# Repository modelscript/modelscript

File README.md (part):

<div align="center"><b>بِسْمِ اللَّهِ الرَّحْمَٰنِ الرَّحِيمِ</b></div>
<div align="center">In the name of Allah, the Compassionate, the Merciful</div>

# ModelScript

ModelScript is a Web-native, polyglot compiler & engineering intelligence platform that unifies **106 open standards and industrial simulation formats** — spanning systems engineering & optimization (ModelScript, Modelica, AMPL, SysML v2, SSP, ReqIF, NIST OSCAL, OWL 2, CSV), power, RF, telecommunications & electronics (PSCAD, PSS/E, CIM / CGMES, OpenDSS, DIgSILENT PowerFactory, GE PSLF, OCPP, OpenADR, SPICE, Verilog-A, IBIS, Touchstone, Optical Transport, RAN & Microwave, Fiber Outside Plant), fluid/process, subsurface, civil water & nuclear (OLGA, PipelineStudio, Aspen Plus, gPROMS, ECLIPSE, EPANET, SWMM, RELAP5, EnergyPlus, HEC-RAS, TOUGH, MODFLOW, LandGEM), multibody/automotive/robotics/rail & transit (ADAMS, SIMPACK, GENSYS, GT-SUITE, SIMA, URDF, OpenDRIVE, OpenSCENARIO, AUTOSAR, GTFS, PLCopen, AutomationML), aerospace & controls (Simulink, EASY5, JSBSim, ROCETS, CCSDS), 3D CAD/CAE & metrology (STEP, ISO 23952 QIF, OpenSCAD, OpenUSD, CalculiX FEA, SU2 CFD), chemistry & systems/synthetic biology (SBML, Antimony, Cantera, SMILES/SDF, NMTRAN, SBOL3, BioNetGen, SED-ML, PDB/mmCIF, GenBank/FASTA, PHREEQC, Fortran, C99), and radiology, radiation oncology & computer-assisted surgery (OpenSim, DICOM-RT, CellML, FEBio/SOFA, NIfTI/NRRD, TOPAS/GATE, 3MF Medical, OpenIGTLink/PLUS) — into a continuous digital thread for end-to-end design, simulation, formal verification, and compliance auditing.

---

## Architecture Highlights

```
┌──────────────────────────────────────────────────────────────────────────────────────────┐
│                                 ModelScript Digital Thread                               │
├──────────────────┬─────────────────┬─────────────────┬─────────────────┬─────────────────┤
│ SysML v2 / ReqIF │ Modelica / SSP  │ STEP / QIF / CAD│ Power / Fluids  │ Bio / Medical / │
│  OSCAL / OWL 2   │ Simulink / EASY5│  (OpenSCAD/FEA) │ (PSCAD/OLGA/+)  │ Aero / Robotics │
└────────┬─────────┴────────┬────────┴────────┬────────┴────────┬────────┴────────┬────────┘
         │                  │                 │                 │                 │
         ▼                  ▼                 ▼                 ▼                 ▼
┌──────────────────────────────────────────────────────────────────────────────────────────┐
│                 Native WebAssembly GLR Incremental Parsers & CST Arenas                  │
├──────────────────────────────────────────────────────────────────────────────────────────┤
│                  Polyglot Triple Graph Grammars (TGG) & AOT Rewriting                    │
│           (Bidirectional forward/backward propagation & Critical Pair Analysis)          │
├──────────────────────────────────────────────────────────────────────────────────────────┤
│                      Salsa Query Engine & Workspace Symbol Index                         │
│                    (Incremental memoization, dependency invalidation)                    │
├──────────────────────────────────────────────────────────────────────────────────────────┤
│                       Semantic Theory Coordinator (Nelson-Oppen)                         │
│   Ontology ─── Constraint/Arithmetic ─── Abstract Domains ─── Continuous Safety ─── CAD  │
├──────────────────────────────────────────────────────────────────────────────────────────┤
│                        Data-Oriented DAE Arena & Solvers                                 │
│   DAEBuilder ── BLT ── SUNDIALS CVODE/IDA ── WebGPU Batched ── Direct Collocation Opt    │
└──────────────────────────────────────────────────────────────────────────────────────────┘
```

### 1. Polyglot Triple Graph Grammars (TGG)

ModelScript features a declarative, AOT-compiled **Triple Graph Grammar (TGG)** and Double-Pushout (DPO) graph rewriting engine (`@modelscript/dsl/tgg`). Rather than relying on fragile manual point-to-point synchronizers, TGG rules declaratively define correspondences between source, target, and correspondence graphs. The engine compiles these rules into high-performance AssemblyScript dispatch tables in WebAssembly (`tgg_forward_dispatch`, `tgg_backward_dispatch`, `tgg_propagate_all_stale`), verified for confluence and termination via integrated **Critical Pair Analysis (CPA)**.

### 2. Semantic Theory Coordinator (Nelson-Oppen Multi-Solver)

Cross-domain verification is orchestrated by a generalized **Nelson-Oppen Semantic Theory Coordinator** (`@modelscript/runtime/formal/theory_coordinator`), exchanging equality facts, tight numeric intervals, and conflict clauses across **19 domain theory oracles** with CDCL(T) case splitting:

- **Ontology Domain (`OntologyTheoryOracle`)**: Tableau Description Logic (DL) reasoner, OWL2 bundle closure, BFO ISO/IEC 21838-2 upper-level semantic alignment (`SemanticProjector`), concept subsumption, and scoped disjointness.
- **Constraint Domain (`ConstraintTheoryOracle`)**: Non-linear interval contraction via HC4 contractor, DPLL(T) arithmetic solver, and variable domain bounding.
- **Abstract Domain (`AbstractDomainOracle`)**: Octagon Difference Bound Matrices (DBM), 4D spatio-temporal intervals, and relational numerical bounds.
- **Continuous Safety & Reliability Domain (`ContinuousSafetyOracle` / `SafetyTheoryOracle`)**: Reachability analysis via zonotopes, constrained zonotopes, star sets, Sum-of-Squares (SOS) barrier certificates, Fault Tree Analysis (FTA), Minimal Cut Sets (MCS), and ISO 26262 / DO-178C safety metrics.
- **Dynamic Simulation Domain (`DynamicSimulationOracle`)**: DAE numerical trajectory integration, Signal Temporal Logic (STL) quantitative robustness monitoring, and tolerance propagation.
- **Spatial Physics Domain (`SpatialPhysicsOracle`)**: Watertight B-Rep CAD solid query, collision/clearance checks, geometric mass properties, 3D verification overlays (reachability tubes, SOS barrier shells, clearance vectors), and 3D FEA/CFD field coupling.
- **CAE Contract Domain (`CaeContractOracle`)**: FEA structural stress/deflection and CFD aerodynamic performance contract verification synchronized with the Digital Thread hypergraph.
- **Causalization Domain (`CausalizationOracle`)**: Pantelides Index-1 structural non-singularity, algebraic loop solvability, and Nyquist-Shannon sampling stability verification.
- **Dimensional Domain (`DimensionalOracle`)**: ISO 80000 7-element rational exponent vector (`[L, M, T, I, Θ, N, J]`) dimensional homogeneity, unit consistency, and cross-domain polyglot drift checking (`checkPolyglotPhysicalDrift`).
- **Entailment Domain (`EntailmentOracle`)**: V-Model requirements decomposition completeness proving ($\bigwedge R_{\text{child},i} \models R_{\text{parent}}$) with signed proof manifest generation.
- **Flow Algebra Domain (`FlowAlgebraOracle`)**: SysML v2 / KerML conjugated port involution (`~Port`), Kirchhoff conservative flow balancing, and 1D–3D CFD boundary flux coupling.
- **Tolerance Stack & UQ Domains (`ToleranceStackOracle`, `UqOracle`)**: STEP AP242 GD&T 1D/3D tolerance chain evaluation (Worst-Case, RSS, Six-Sigma $C_{pk}$) and stochastic Uncertainty Quantification via analytical CDFs and Monte Carlo sampling.
- **Radiology & Surgical CAS Domain (`RadiologyCasTheoryOracle`)**: QUANTEC organ-at-risk (OAR) radiotherapy DVH/BED/EQD2 dose constraints, Hadrontherapy Bragg peak range verification, $SE(3)$ surgical navigation transform orthogonality, Fitzpatrick Target Registration Error ($\text{TRE}$), and 2-manifold patient-specific cutting guide safety checks.
- **Additional Domain Oracles**: `ArrayTheoryOracle` (array read-over-write axioms), `BitVectorTheoryOracle` (fixed-width bit-vector arithmetic), `StringTheoryOracle` (string & regex constraints), `PowerGridTheoryOracle` (AC power flow & grid stability), `TelecomTheoryOracle` (RF MPE, DWDM GSNR & siting), `MarineMooringTheoryOracle` (catenary mooring & DNV-OS-E301), and `PressureVesselOracle` (ASME BPVC Sec. VIII Div. 1 pressure vessel rules) — see [`packages/runtime/README.md`](./packages/runtime/README.md).

### 3. Data-Oriented Linear Memory Simulation (DAE Arena)

The simulation runtime employs a zero-allocation Struct-of-Arrays (SoA) layout (`DAEBuilder`) in linear WebAssembly memory. Equations, variables, and expressions are lowered directly from linear parser CST nodes into integer arena handles, enabling microsecond Pantelides index reduction, Tarjan BLT partition sorting, alias elimination, Implicitly Restarted Arnoldi sparse eigenvalue extraction, and SIMD/WebGPU batched numerical solving without garbage collection overhead.

### 4. Salsa-Based Incremental Computation

Inspired by Rust's Salsa, compilation, name resolution, and specialized class instances are fully memoized on a demand-driven dependency graph. When an engineer modifies a single equation or parameter, only transitively affected queries and DAE blocks are re-flattened.

---

## Supported Languages & Domain Capabilities (106 Languages)

ModelScript provides first-class support for **106 engineering languages and simulation formats** under `languages/`, organized across 8 domain clusters and powered by native WebAssembly parsers, linear-memory CST arenas, static pre-flight linters, and direct `DAEBuilder` lowering.

> **Maturity Tiers** (enforced in `package.json#modelscript.tier` via `pnpm run lint:manifests` and audited via `pnpm run audit:languages`):
>
> - **`Beta` (33 languages)** — Production-ready with complete WASM GLR parser, static linter, DAE/solver lowering, and $\ge 8$ test suites verified against standard industry benchmarks or standard library snapshots (e.g., OpenModelica & MSL 4.1.0, OMG KerML standard library, IEEE/WECC power grids, US EPA EPANET/SWMM, Manchester Benchmark / EN 14363, NASA ROCETS / CCSDS).
> - **`Alpha` (72 languages)** — Domain-complete with native WASM parser, static domain linter, `DAEBuilder`/solver lowering, and $\ge 5$ unit/integration and benchmark test suites.
> - **`Pre-Alpha` (1 language: [`las`](./languages/las/))** — Early-stage native WASM parser and DAE lowering undergoing 6-pillar verification.

### 1. Native & Core Systems Engineering (11)

| Language & Directory                                                    | Extensions                 | Maturity | Domain & Core Capabilities                                                                                                                                                                                                                                           |
| :---------------------------------------------------------------------- | :------------------------- | :------: | :------------------------------------------------------------------------------------------------------------------------------------------------------------------------------------------------------------------------------------------------------------------- |
| **ModelScript**<br>[`languages/modelscript/`](./languages/modelscript/) | `.msx`                     |  `Beta`  | Unified declarative multi-domain language combining acausal physical equations, hierarchical state machines, spatial CAD constraints, and direct compilation to the WebAssembly DAE arena.                                                                           |
| **Modelica**<br>[`languages/modelica/`](./languages/modelica/)          | `.mo`                      |  `Beta`  | Complete Modelica 3.x equation-based modeling; native AssemblyScript flattening kernel (`ModelicaFlattener`) supporting `hybrid`, `wasm`, `ts`, and `diff` modes; connector balancing; BLT partitioning; and OMC conformance.                                        |
| **AMPL**<br>[`languages/ampl/`](./languages/ampl/)                      | `.mod`, `.dat`, `.nl`      |  `Beta`  | Algebraic modeling language for mathematical optimization (LP, MILP, NLP, MINLP), relational set and multidimensional array unrolling, automatic differentiation tape lowering, ASL `.nl` / MPS interchange, and native COIN-OR (CLP/CBC/IPOPT) WebAssembly solving. |
| **SysML v2 / KerML**<br>[`languages/sysml2/`](./languages/sysml2/)      | `.sysml`, `.kerml`         |  `Beta`  | OMG Systems Modeling Language v2 & KerML parsing, standard library snapshot, structural part/port definitions, state machine & fUML activity execution, decision table verification, and requirements allocation.                                                    |
| **SSP 1.0**<br>[`languages/ssp/`](./languages/ssp/)                     | `.ssp`, `.ssd`, `.ssv`     |  `Beta`  | System Structure and Parameterization standard packaging, multi-FMU co-simulation topologies (`SystemStructure.ssd`), parameter value catalogs (`.ssv`), and signal dictionary mappings (`.ssm`).                                                                    |
| **ReqIF**<br>[`languages/reqif/`](./languages/reqif/)                   | `.reqif`, `.reqifz`        |  `Beta`  | OMG Requirements Interchange Format v1.2 parsing, `SPEC-OBJECTS` / `SPEC-RELATIONS` traceability graph extraction, suspect-link detection, and bidirectional SysML v2 requirement synchronization.                                                                   |
| **MagicDraw**<br>[`languages/magicdraw/`](./languages/magicdraw/)       | `.mdzip`, `.mdxml`, `.xmi` |  `Beta`  | MagicDraw / Cameo Systems Modeler `.mdzip` archive & OMG UML 2.x / SysML 1.x XMI parsing, clean-room OMG standard profiles & QUDV units, BDD/IBD/REQ/PAR/STM diagram rendering, lints (`M9921`–`M9934`), and SysML v2 / ReqIF / Modelica / DAE projections.          |
| **NIST OSCAL**<br>[`languages/oscal/`](./languages/oscal/)              | `.json`, `.xml`            | `Alpha`  | NIST Open Security Controls Assessment Language (OSCAL 1.1.x) parsing, SP 800-53 rev 5 catalog baseline resolution, Cyber-Physical Systems (CPS) security control mapping, and regulatory compliance verification.                                                   |
| **OWL 2**<br>[`languages/owl2/`](./languages/owl2/)                     | `.owl`, `.ofn`             |  `Beta`  | W3C OWL 2 Functional-Style Syntax parsing, Tableau Description Logic (DL) reasoning, BFO ISO/IEC 21838-2 alignment, concept subsumption, Manchester syntax rendering, OWL 2 DL/EL profile linting, and SPARQL-DL querying.                                           |
| **SPARQL 1.1**<br>[`languages/sparql/`](./languages/sparql/)            | `.rq`, `.sparql`           |  `Beta`  | Native W3C SPARQL 1.1 Query & Update WASM GLR parser, algebra compiler, generalized Leapfrog Triejoin (WCOJ) engine, and direct triple-store adapters (`WasmOntologyReasoner`, `WasmOntologyStore`, `PagedStorageEngine`, `SqliteRdfSource`).                        |
| **CSV**<br>[`languages/csv/`](./languages/csv/)                         | `.csv`                     |  `Beta`  | High-throughput tabular data parsing, RFC 4180 structural linting, experimental sensor telemetry ingestion, trajectory regression comparison, and parameter calibration datasets.                                                                                    |

### 2. Electrical Power Grids, RF, Telecommunications & Electronics (32)

| Language & Directory                                                       | Extensions                                             | Maturity | Domain & Core Capabilities                                                                                                                                                                                                                                                                                             |
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
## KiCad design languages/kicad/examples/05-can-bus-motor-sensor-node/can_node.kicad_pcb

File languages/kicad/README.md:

<div align="center"><b>بِسْمِ اللَّهِ الرَّحْمَٰنِ الرَّحِيمِ</b></div>
<div align="center">In the name of Allah, the Compassionate, the Merciful</div>

# @modelscript/kicad

**Maturity:** Beta · **Extensions:** `.kicad_pcb`, `.kicad_sch`, `.kicad_sym`, `.kicad_mod` · **Docs:** [modelscript.org/languages/kicad](https://modelscript.org/languages/kicad)

KiCad 6/7/8/9 ECAD language package (`.kicad_pcb`, `.kicad_sch`, `.kicad_sym`, `.kicad_mod`) for ModelScript.

## Capabilities

- **Native WebAssembly GLR Parser (`dist/parser.wasm`):** Unified S-expression grammar compiled via `@modelscript/dsl`.
- **`.kicad_pcb` & `.kicad_sch` Parser:** Extracts layers, dielectric stackup, nets, footprints (with rotated pad-to-board coordinate transforms), traces, arcs, vias, copper zones, `Edge.Cuts` outlines, and schematic symbols/wires/labels.
- **`@modelscript/cad` Bridge (`kicadBoardToPcbLayout`):** Lowers parsed KiCad boards directly into ModelScript's canonical `PCBLayout` + `NetlistGraph`, enabling `runDRC()`, 3D PCBA enclosure clearance, and manufacturing export (Gerber, ODB++, IPC-2581C).
- **Round-Trip Exporter (`exportToKiCadPcb`):** Emits valid KiCad 8 `.kicad_pcb` S-expressions from `PCBLayout`.
- **Geometric Schematic Netlist & ERC (`extractSchematicNetlist`, `lintKiCadSchematic`):** Resolves `.kicad_sch` `lib_symbols`, wires, junctions, labels, and power symbols into `NetlistGraph` with ERC checks (`K2002`–`K4003`).
- **Direct MNA `DAEBuilder` Lowering (`lowerKiCadSchematicToDAE`):** Lowers resistors, capacitors, inductors, and DC sources directly into ModelScript's linear-memory `DAEBuilder`.
- **Layout-Aware RLGC & Impedance (`extractBoardParasitics`):** Computes DC resistance, Hammerstad-Jensen microstrip/stripline $Z_0$, lumped $L/C$, propagation delay, and IPC-2221 ampacity from board stackup and trace geometry.
- **Schematic ↔ PCB Consistency & Cross-File LSP (`verifySchematicPcbConsistency`, `resolveKiCadHover`, `findCrossFileDefinition`):** Detects missing/orphan components, value/footprint drift, and pin-net mismatches (`K2010`–`K2014`), plus cross-file navigation and parasitic-enriched hover.

## Package Structure

| File                           | Responsibility                                                                                    |
| ------------------------------ | ------------------------------------------------------------------------------------------------- |
| `src/language.ts`              | `@modelscript/dsl` language registration (`.kicad_pcb`, `.kicad_sch`, `.kicad_sym`, `.kicad_mod`) |
| `src/grammar/kicad-grammar.ts` | Unified KiCad S-expression grammar for WASM GLR parser generation                                 |
| `src/parser/kicad-parser.ts`   | KiCad board, schematic, symbol, and footprint S-expression parser                                 |
| `src/cad-bridge.ts`            | `kicadBoardToPcbLayout` lowering into `@modelscript/cad` `PCBLayout`                              |
| `src/export.ts`                | `exportToKiCadPcb` round-trip KiCad 8 `.kicad_pcb` exporter                                       |
| `src/schematic-netlist.ts`     | `extractSchematicNetlist` geometric wire/junction/label netlist extractor                         |
| `src/hierarchy.ts`             | Hierarchical multi-sheet schematic resolver                                                       |
| `src/parasitics.ts`            | `extractBoardParasitics` RLGC, microstrip/stripline $Z_0$, and IPC-2221 ampacity engine           |
| `src/consistency.ts`           | `verifySchematicPcbConsistency` schematic-to-PCB drift & pin-net checker                          |
| `src/dae/dae-lower.ts`         | `lowerKiCadSchematicToDAE` direct MNA lowering into `DAEBuilder`                                  |
| `src/lints/index.ts`           | `lintKiCadSchematic` ERC and consistency lint rules (`K2002`–`K4003`)                             |
| `src/lsp.ts`                   | Cross-file LSP hover, go-to-definition, and diagnostics                                           |
| `src/indexing.ts`              | Workspace symbol indexing across KiCad schematics and boards                                      |
| `src/index.ts`                 | Public package entry point and barrel exports                                                     |

## Scripts

```bash
pnpm --filter @modelscript/kicad build
pnpm --filter @modelscript/kicad test
pnpm --filter @modelscript/kicad lint
pnpm --filter @modelscript/kicad typecheck
```

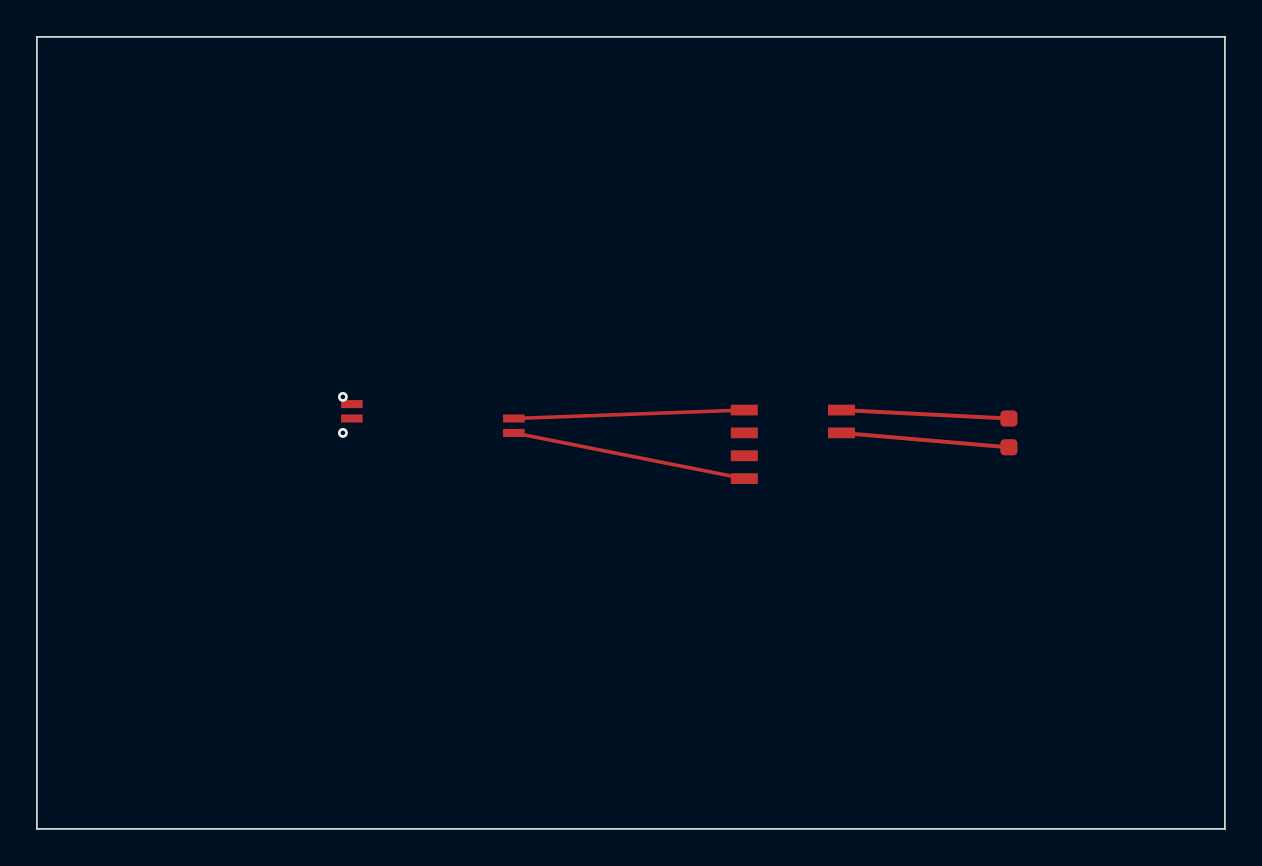
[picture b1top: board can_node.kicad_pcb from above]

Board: 4 copper layers, 66.0 x 44.0 mm, 3 parts (0 on the bottom side), 6 nets.

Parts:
R1: 120; R_0603
U1: STM32G431; LQFP-32
U2: TCAN1042; SOIC-8

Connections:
CANH: R1.1, U2.7
CANL: R1.2, U2.6
CAN_RX: U1.16, U2.4
CAN_TX: U1.15, U2.1
GND: U1.2, U2.2
VDD_3V3: U1.1, U2.3

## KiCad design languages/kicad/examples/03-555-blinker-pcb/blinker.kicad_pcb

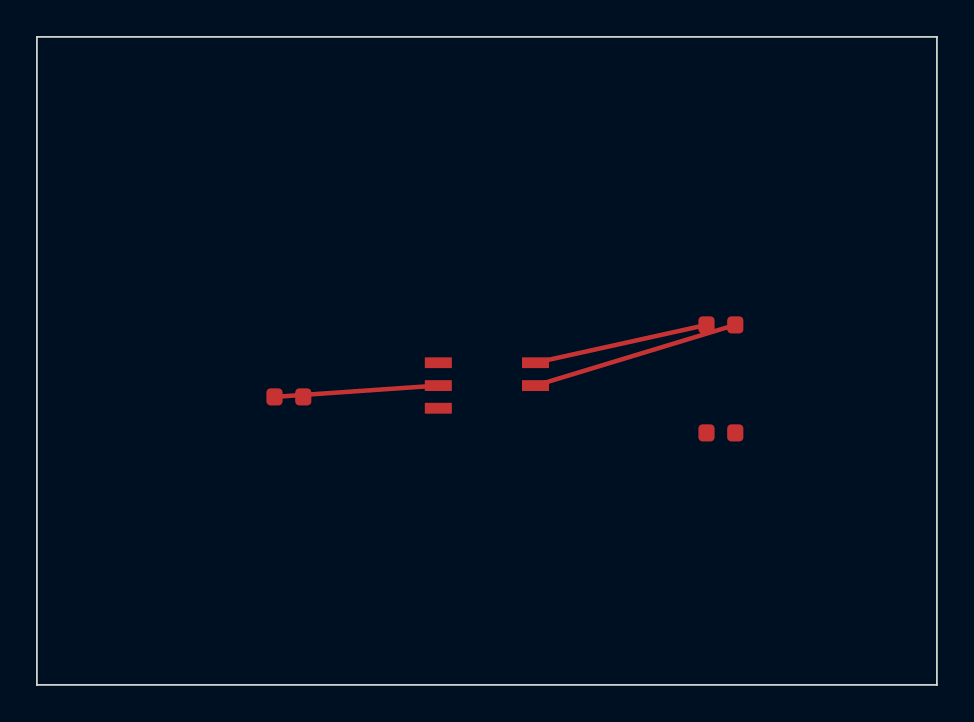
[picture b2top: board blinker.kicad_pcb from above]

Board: 2 copper layers, 50.0 x 36.0 mm, 4 parts (0 on the bottom side), 4 nets.

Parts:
C1: 10uF; C_0603
R1: 10k; R_0603
R2: 47k; R_0603
U1: NE555; SOIC-8

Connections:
DISCH: R1.2, R2.1, U1.7
GND: C1.2, U1.1
TRIG: C1.1, R2.2, U1.2
VCC: R1.1, U1.8

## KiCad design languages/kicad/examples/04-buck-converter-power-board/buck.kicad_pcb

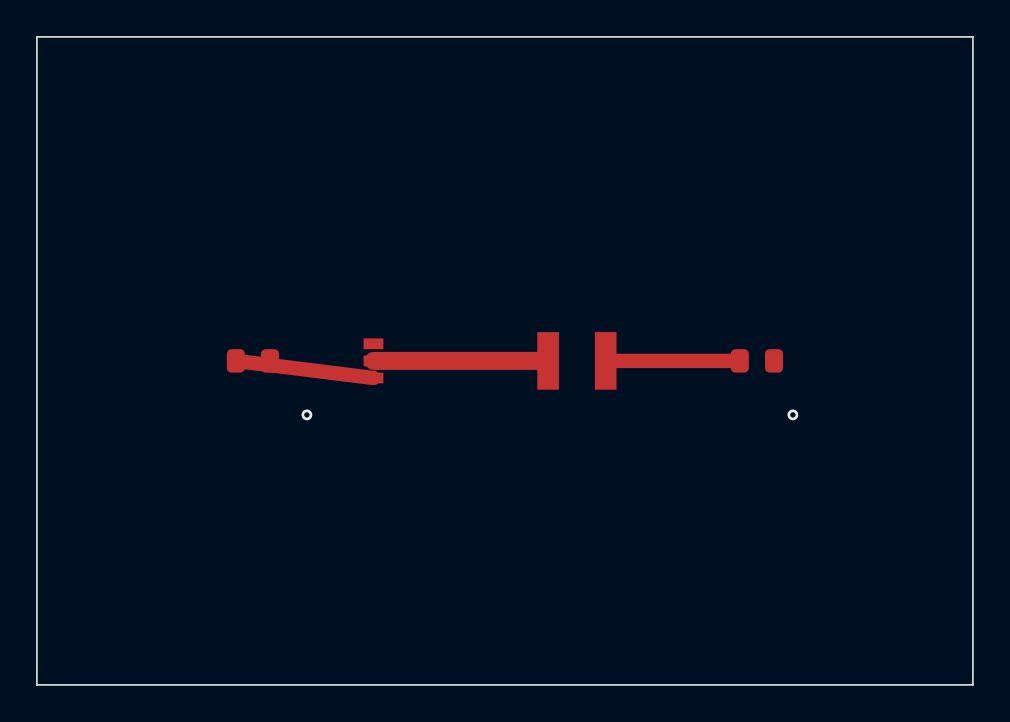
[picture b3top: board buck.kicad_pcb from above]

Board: 2 copper layers, 52.0 x 36.0 mm, 4 parts (0 on the bottom side), 4 nets.

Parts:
C1: 22uF; C_0805
C2: 47uF; C_0805
L1: 4.7uH; L_4020
U1: TPS563201; SOT-23-6

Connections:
GND: C1.2, C2.2, U1.1
SW: L1.1, U1.2
VIN_5V: C1.1, U1.3
VOUT_3V3: C2.1, L1.2

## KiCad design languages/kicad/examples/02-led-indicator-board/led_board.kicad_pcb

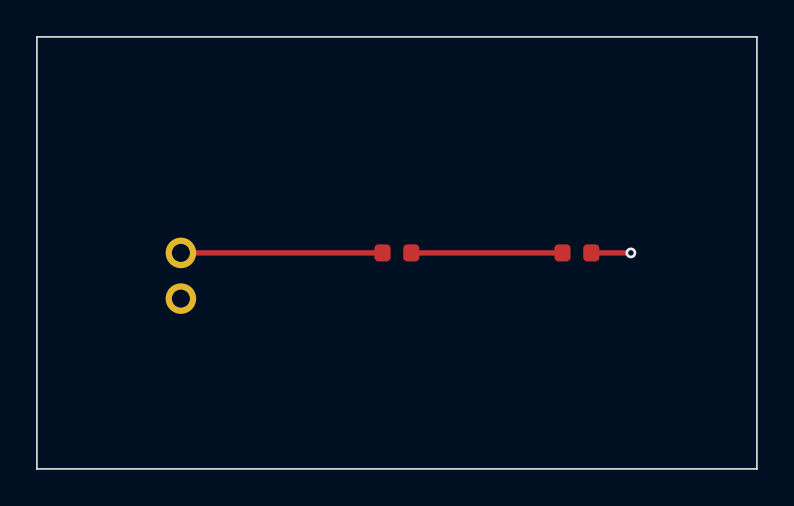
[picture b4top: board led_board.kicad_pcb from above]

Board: 2 copper layers, 40.0 x 24.0 mm, 3 parts (0 on the bottom side), 3 nets.

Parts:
D1: GREEN; LED_0603_1608Metric
J1: 5V_IN; PinHeader_1x02
R1: 330; R_0603_1608Metric

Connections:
GND: D1.2, J1.2
LED_A: D1.1, R1.2
V5V: J1.1, R1.1

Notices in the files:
README.md:
License:
ModelScript follows an **Open-Core and Dual-License** model:
- **Community Edition (Open Core)**: All packages under `packages/`, `languages/`, and `apps/` are licensed under the **GNU Affero General Public License v3.0 or later (`AGPL-3.0-or-later`)**. See [`COPYING`](./COPYING) for the full license text.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
([`ee/`](./ee/))**: All files inside `ee/` (`@modelscript/ee`) and the pre-hardened Enterprise Intranet Appliance (`ee/deploy/`) are proprietary and licensed under the **ModelScript Enterprise License (`LicenseRef-ModelScript-Enterprise`)**.
